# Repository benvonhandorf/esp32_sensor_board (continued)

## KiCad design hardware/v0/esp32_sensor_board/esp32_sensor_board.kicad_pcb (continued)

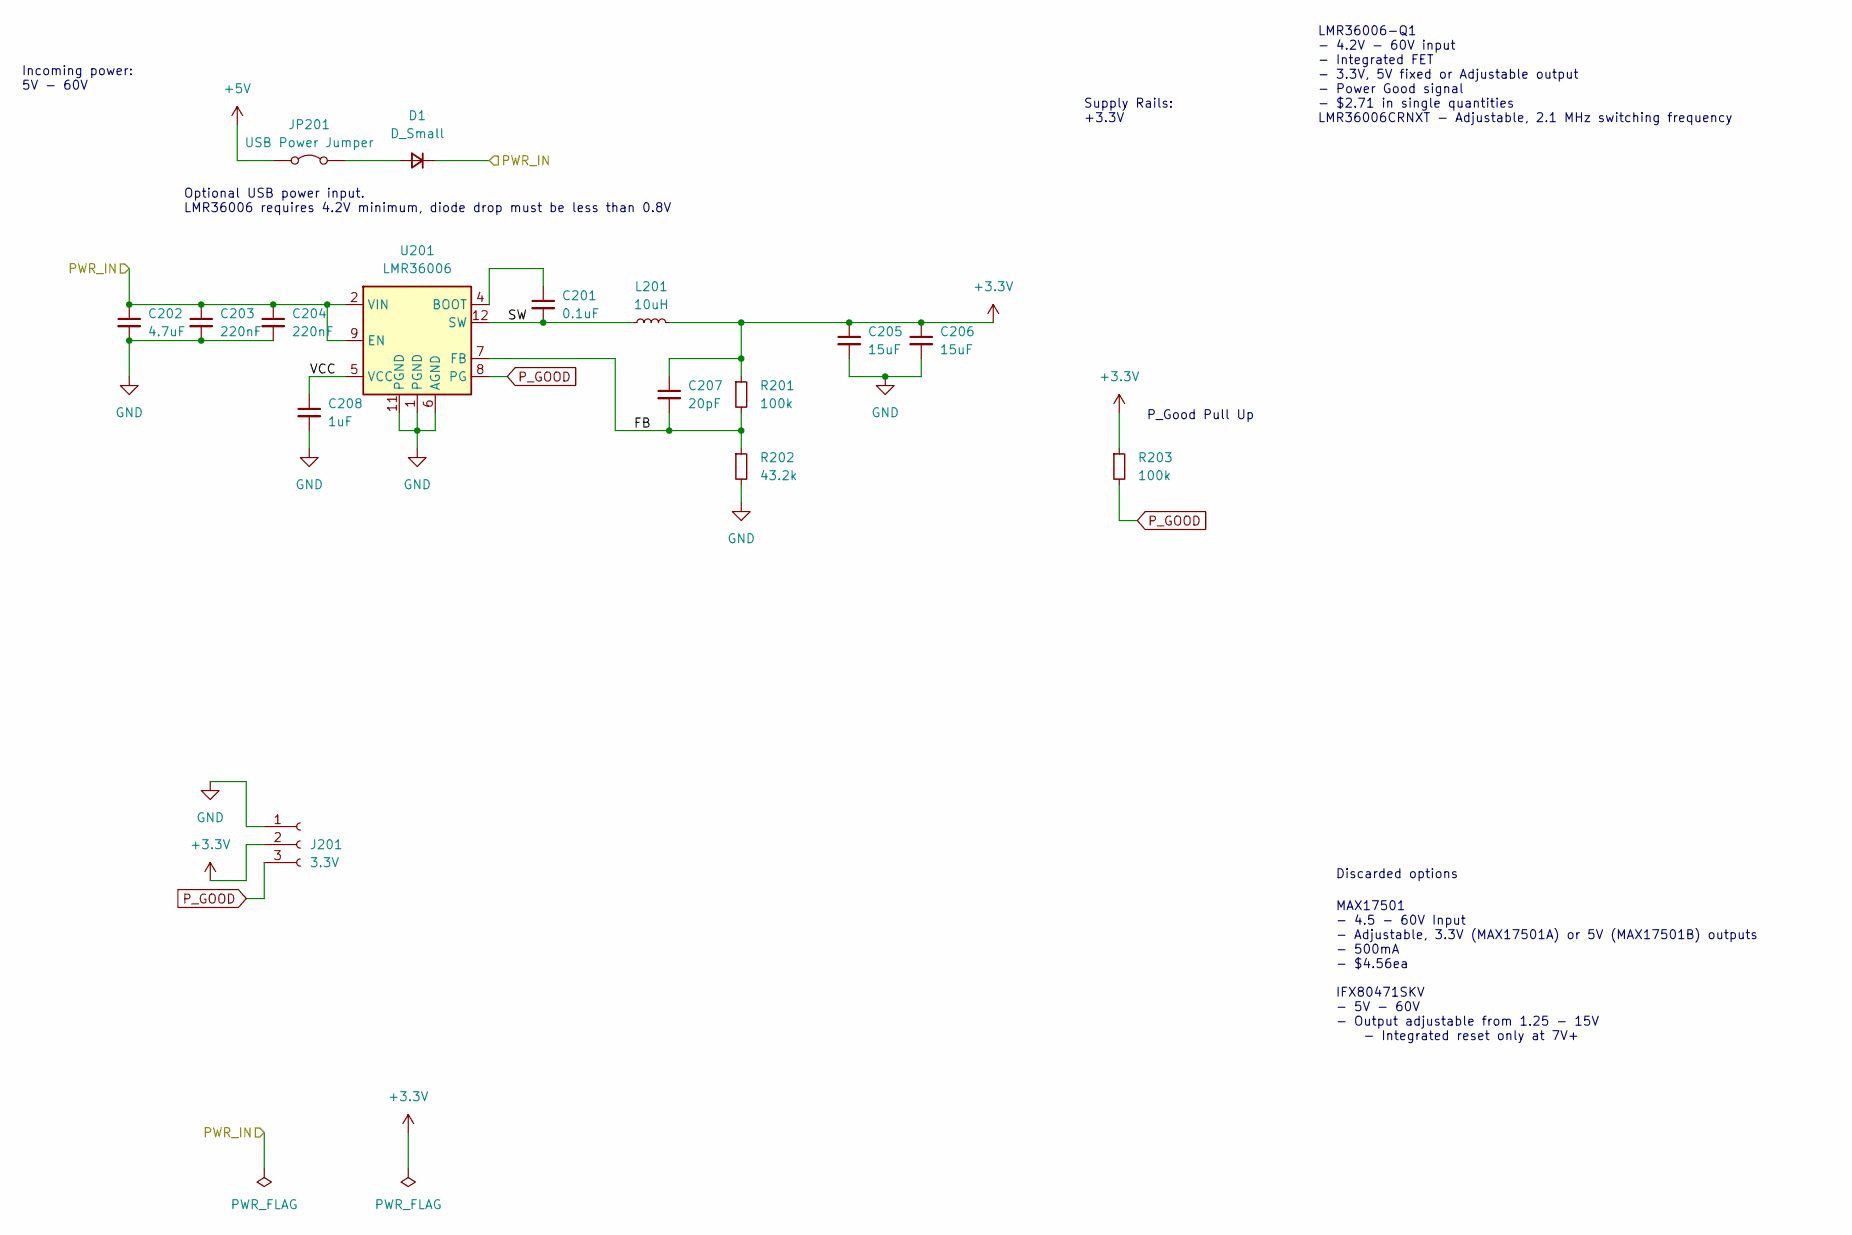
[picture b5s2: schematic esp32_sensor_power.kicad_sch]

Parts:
C201: 0.1uF; C_0603_1608Metric
C202: 4.7uF; C_1206_3216Metric
C203, C204: 220nF; C_1206_3216Metric
C205, C206: 15uF; C_1206_3216Metric
C207: 20pF; C_0805_2012Metric
C208: 1uF; C_0805_2012Metric
D1: D_Small; D_SOD-123
J201: 3.3V; PinHeader_1x03_P2.54mm_Vertical
JP201: USB Power Jumper; SolderJumper-2_P1.3mm_Bridged_RoundedPad1.0x1.5mm
L201: 10uH; L_Taiyo-Yuden_MD-4040
R201, R203: 100k; R_0603_1608Metric
R202: 43.2k; R_0603_1608Metric
U201: LMR36006; LMR36006-VQFN-HR

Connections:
+3.3V: C205.1, C206.1, C207.1, J201.2, L201.2, R201.1, R203.1; also elsewhere on the board
+5V: JP201.1 (A); also elsewhere on the board
/Power/FB: C207.2, R201.2, R202.1, U201.7 (FB)
/Power/SW: C201.2, L201.1, U201.3 (SW), U201.12 (SW)
/Power/VCC: C208.1, U201.5 (VCC)
GND: C202.2, C203.2, C204.2, C205.2, C206.2, C208.2, J201.1, R202.2, U201.1 (PGND), U201.6 (AGND), U201.11 (PGND); also elsewhere on the board
unnamed: D1.2 (A), JP201.2 (B)
unnamed: C201.1, U201.4 (BOOT)
P_GOOD: J201.3, R203.2, U201.8 (PG)
VIN: C202.1, C203.1, C204.1, D1.1 (K), U201.2 (VIN), U201.9 (EN), U201.10 (VIN); also elsewhere on the board

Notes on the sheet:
MAX17501 - 4.5 - 60V Input - Adjustable, 3.3V (MAX17501A) or 5V (MAX17501B) outputs - 500mA - $4.56ea
LMR36006-Q1 - 4.2V - 60V input - Integrated FET - 3.3V, 5V fixed or Adjustable output - Power Good signal - $2.71 in single quantities LMR36006CRNXT - Adjustable, 2.1 MHz switching frequency
IFX80471SKV - 5V - 60V - Output adjustable from 1.25 - 15V - Integrated reset only at 7V+
P_Good Pull Up
Discarded options
Optional USB power input. LMR36006 requires 4.2V minimum, diode drop must be less than 0.8V
Supply Rails: +3.3V
Incoming power: 5V - 60V

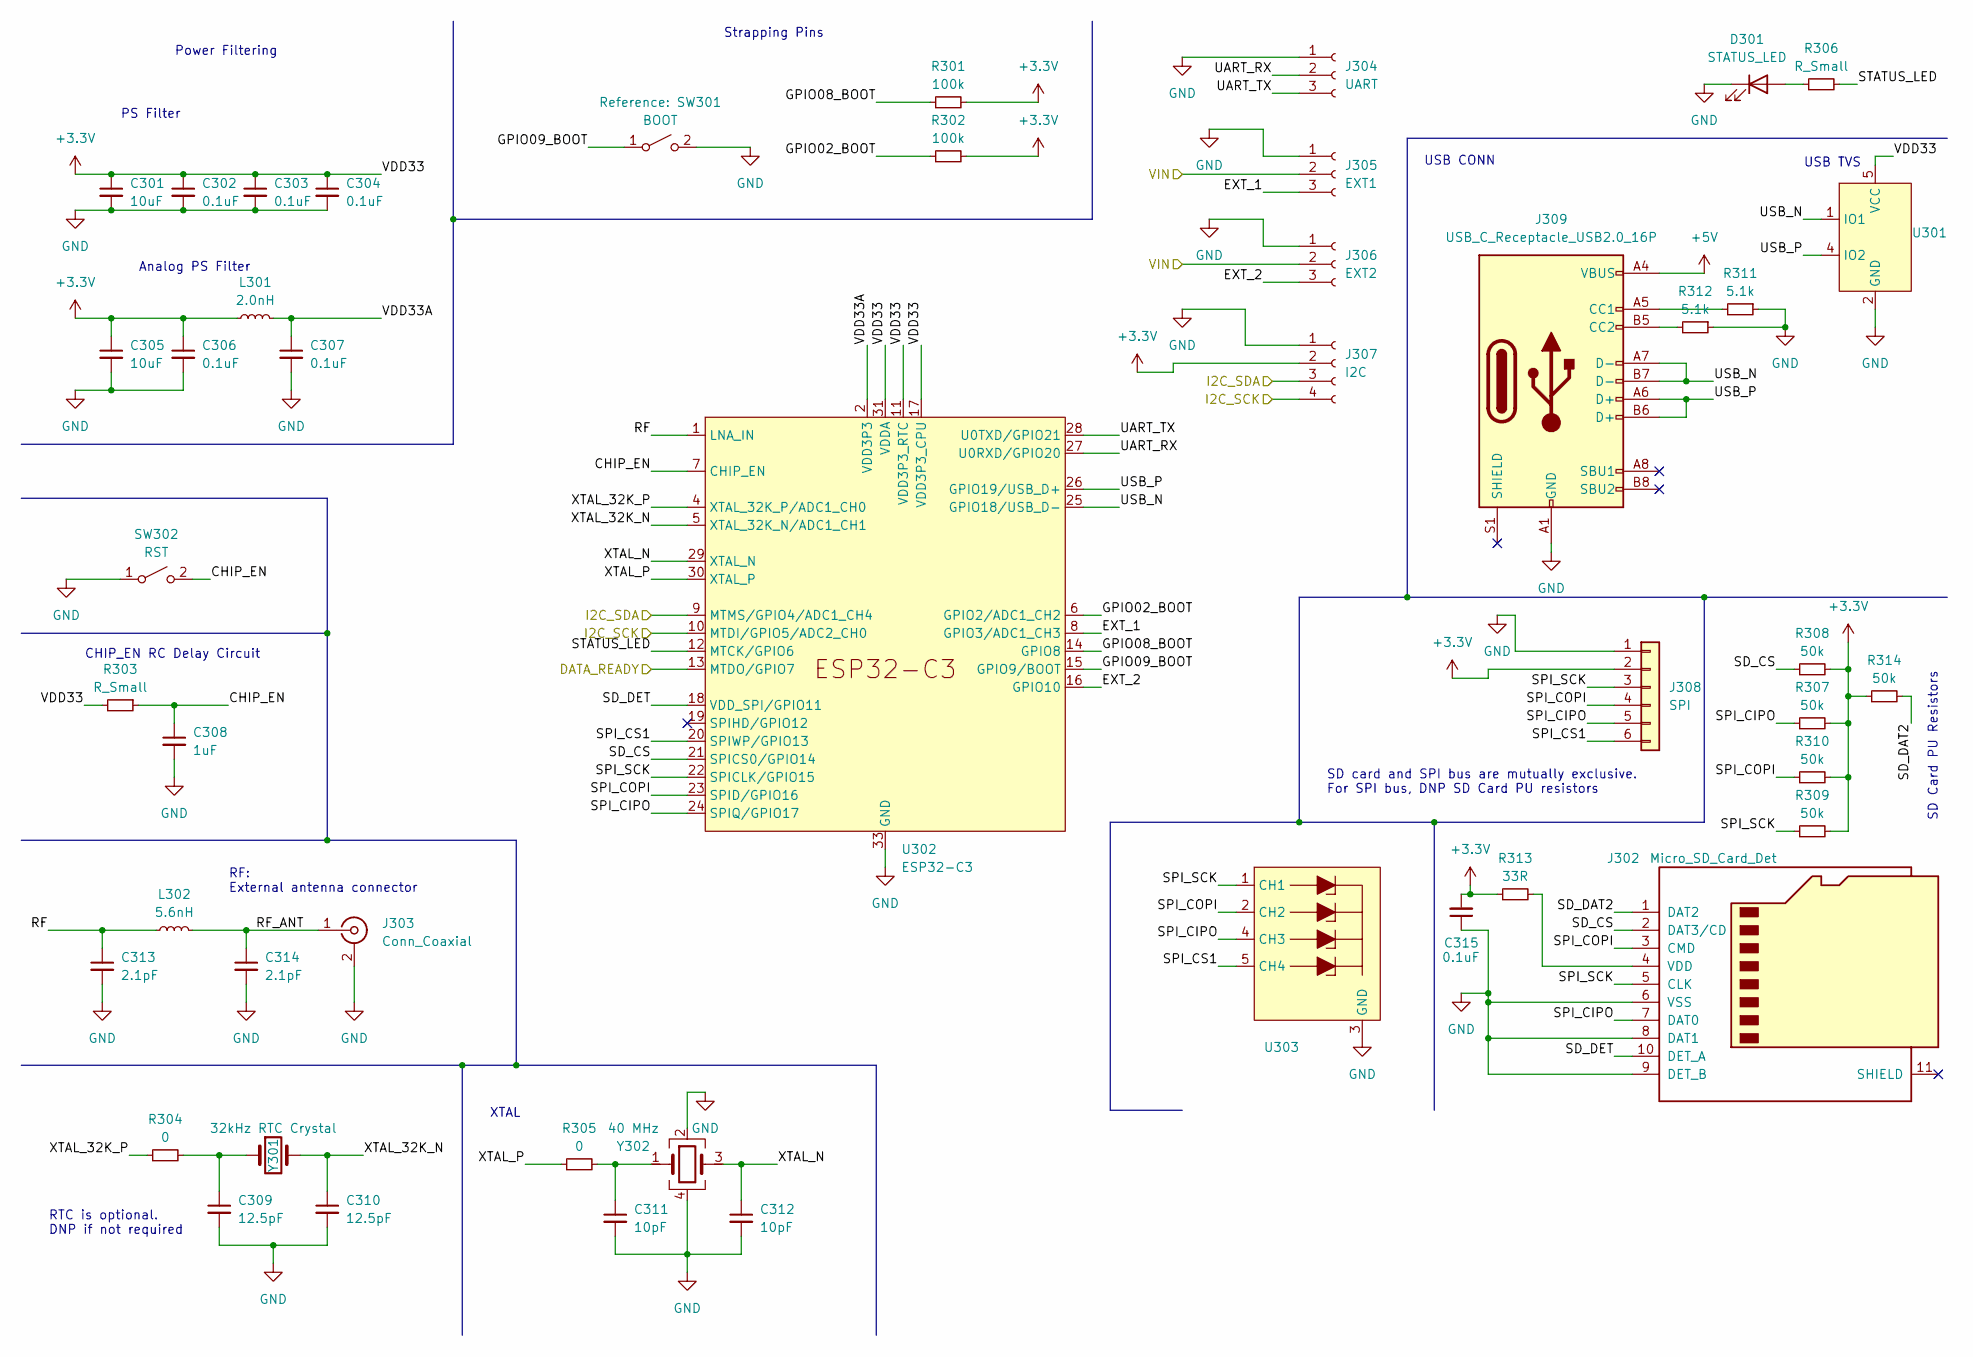
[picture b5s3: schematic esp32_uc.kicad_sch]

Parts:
C301, C305: 10uF; C_0805_2012Metric
C302, C303, C304, C306, C307, C315: 0.1uF; C_0603_1608Metric
C308: 1uF; C_0805_2012Metric
C309, C310: 12.5pF; C_0603_1608Metric
C311, C312: 10pF; C_0603_1608Metric
C313, C314: 2.1pF; C_0603_1608Metric
D301: STATUS_LED; LED_0805_2012Metric
J302: Micro_SD_Card_Det; MicroSD_Socket_Unbranded
J303: Conn_Coaxial; U.FL_Molex_MCRF_73412-0110_Vertical
J304: UART; PinHeader_1x03_P2.54mm_Vertical
J305: EXT1; PinHeader_1x03_P2.54mm_Vertical
J306: EXT2; PinHeader_1x03_P2.54mm_Vertical
J307: I2C; PinHeader_1x04_P2.54mm_Vertical
J308: SPI; PinHeader_1x06_P2.54mm_Vertical
J309: USB_C_Receptacle_USB2.0_16P; USB_C_Receptacle_GCT_USB4085
L301: 2.0nH; L_0402_1005Metric
L302: 5.6nH; L_0603_1608Metric
R301, R302: 100k; R_0603_1608Metric
R303, R306: R_Small; R_0603_1608Metric
R304, R305: 0; R_0603_1608Metric
R307, R308, R309, R310, R314: 50k; R_0603_1608Metric
R311, R312: 5.1k; R_0603_1608Metric
R313: 33R; R_0603_1608Metric
SW301: BOOT; TacButton_SMD_5mm_5mm
SW302: RST; Tac_SMD_6.4mm_Side_SPST_NO
U301: SOT-23-6
U302: ESP32-C3; QFN-32-1EP_5x5mm_P0.5mm_EP3.45x3.45mm
U303: Diode_10Pin_DFN2510A-10_10-XFDFN_SOT1176-1
Y301: 32kHz RTC Crystal; Crystal_SMD_3215-2Pin_3.2x1.5mm
Y302: 40 MHz; Crystal_SMD_2016-4Pin_2.0x1.6mm

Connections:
+3.3V: C301.1, C302.1, C303.1, C304.1, C305.1, C306.1, C315.2, J307.2, J308.2, L301.1, R301.2, R302.2, R303.2, R307.2, R308.2, R309.2, R310.2, R313.1, R314.1, U301.5 (VCC), U302.11 (VDD3P3_RTC), U302.17 (VDD3P3_CPU), U302.31 (VDDA), U302.32 (VDDA); also elsewhere on the board
+5V: J309.A4 (VBUS), J309.A9 (VBUS), J309.B4 (VBUS), J309.B9 (VBUS); also elsewhere on the board
/Load Cell Sensor/DRDY_NAU: U302.13 (MTDO/GPIO7); also elsewhere on the board
/Microprocessor/CHIP_EN: C308.1, R303.1, SW302.2 (B), U302.7 (CHIP_EN)
/Microprocessor/EXT_1: J305.3, U302.8 (GPIO3/ADC1_CH3)
/Microprocessor/EXT_2: J306.3, U302.16 (GPIO10)
/Microprocessor/GPIO02_BOOT: R302.1, U302.6 (GPIO2/ADC1_CH2)
/Microprocessor/GPIO08_BOOT: R301.1, U302.14 (GPIO8)
/Microprocessor/GPIO09_BOOT: SW301.1 (A), U302.15 (GPIO9/BOOT)
/Microprocessor/RF: C313.1, L302.1, U302.1 (LNA_IN)
/Microprocessor/RF_ANT: C314.1, J303.1 (In), L302.2
/Microprocessor/SD_CS: J302.2 (DAT3/CD), R308.1, U302.21 (SPICS0/GPIO14)
/Microprocessor/SD_DAT2: J302.1 (DAT2), R314.2
/Microprocessor/SD_DET: J302.10 (DET_A), U302.18 (VDD_SPI/GPIO11)
/Microprocessor/SPI_CIPO: J302.7 (DAT0), J308.5, R307.1, U302.24 (SPIQ/GPIO17), U303.4 (CH3)
/Microprocessor/SPI_COPI: J302.3 (CMD), J308.4, R310.1, U302.23 (SPID/GPIO16), U303.2 (CH2)
/Microprocessor/SPI_CS1: J308.6, U302.20 (SPIWP/GPIO13), U303.5 (CH4)
/Microprocessor/SPI_SCK: J302.5 (CLK), J308.3, R309.1, U302.22 (SPICLK/GPIO15), U303.1 (CH1)
/Microprocessor/STATUS_LED: R306.2, U302.12 (MTCK/GPIO6)
/Microprocessor/UART_RX: J304.2, U302.27 (U0RXD/GPIO20)
/Microprocessor/UART_TX: J304.3, U302.28 (U0TXD/GPIO21)
/Microprocessor/USB_N: J309.A7 (D-), J309.B7 (D-), U301.1 (IO1), U302.25 (GPIO18/USB_D-)
/Microprocessor/USB_P: J309.A6 (D+), J309.B6 (D+), U301.4 (IO2), U302.26 (GPIO19/USB_D+)
/Microprocessor/VDD33A: C307.1, L301.2, U302.2 (VDD3P3), U302.3 (VDD3P3)
/Microprocessor/XTAL_32K_N: C310.1, U302.5 (XTAL_32K_N/ADC1_CH1), Y301.2
/Microprocessor/XTAL_32K_P: R304.1, U302.4 (XTAL_32K_P/ADC1_CH0)
/Microprocessor/XTAL_N: C312.1, U302.29 (XTAL_N), Y302.3
/Microprocessor/XTAL_P: R305.1, U302.30 (XTAL_P)
/Power Measurement/I2C_SCL: J307.4, U302.10 (MTDI/GPIO5/ADC2_CH0); also elsewhere on the board
/Power Measurement/I2C_SDA: J307.3, U302.9 (MTMS/GPIO4/ADC1_CH4); also elsewhere on the board
GND: C301.2, C302.2, C303.2, C304.2, C305.2, C306.2, C307.2, C308.2, C309.2, C310.2, C311.2, C312.2, C313.2, C314.2, C315.1, D301.1 (K), J302.6 (VSS), J302.8 (DAT1), J302.9 (DET_B), J303.2 (Ext), J304.1, J305.1, J306.1, J307.1, J308.1, J309.A1 (GND), J309.A12 (GND), J309.B1 (GND), J309.B12 (GND), R311.1, R312.1, SW301.2 (B), SW302.1 (A), U301.2 (GND), U302.33 (GND), U303.3 (GND), U303.8 (GND), Y302.2, Y302.4; also elsewhere on the board
unnamed: C309.1, R304.2, Y301.1
unnamed: C311.1, R305.2, Y302.1
unnamed: D301.2 (A), R306.1
unnamed: J302.4 (VDD), R313.2
unnamed: J309.A5 (CC1), R311.2
unnamed: J309.B5 (CC2), R312.2
VIN: J305.2, J306.2; also elsewhere on the board

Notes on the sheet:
CHIP_EN RC Delay Circuit
Analog PS Filter
SD Card PU Resistors
XTAL
USB CONN
SD card and SPI bus are mutually exclusive. For SPI bus, DNP SD Card PU resistors
RTC is optional. DNP if not required
USB TVS
Strapping Pins
Power Filtering
PS Filter
RF: External antenna connector

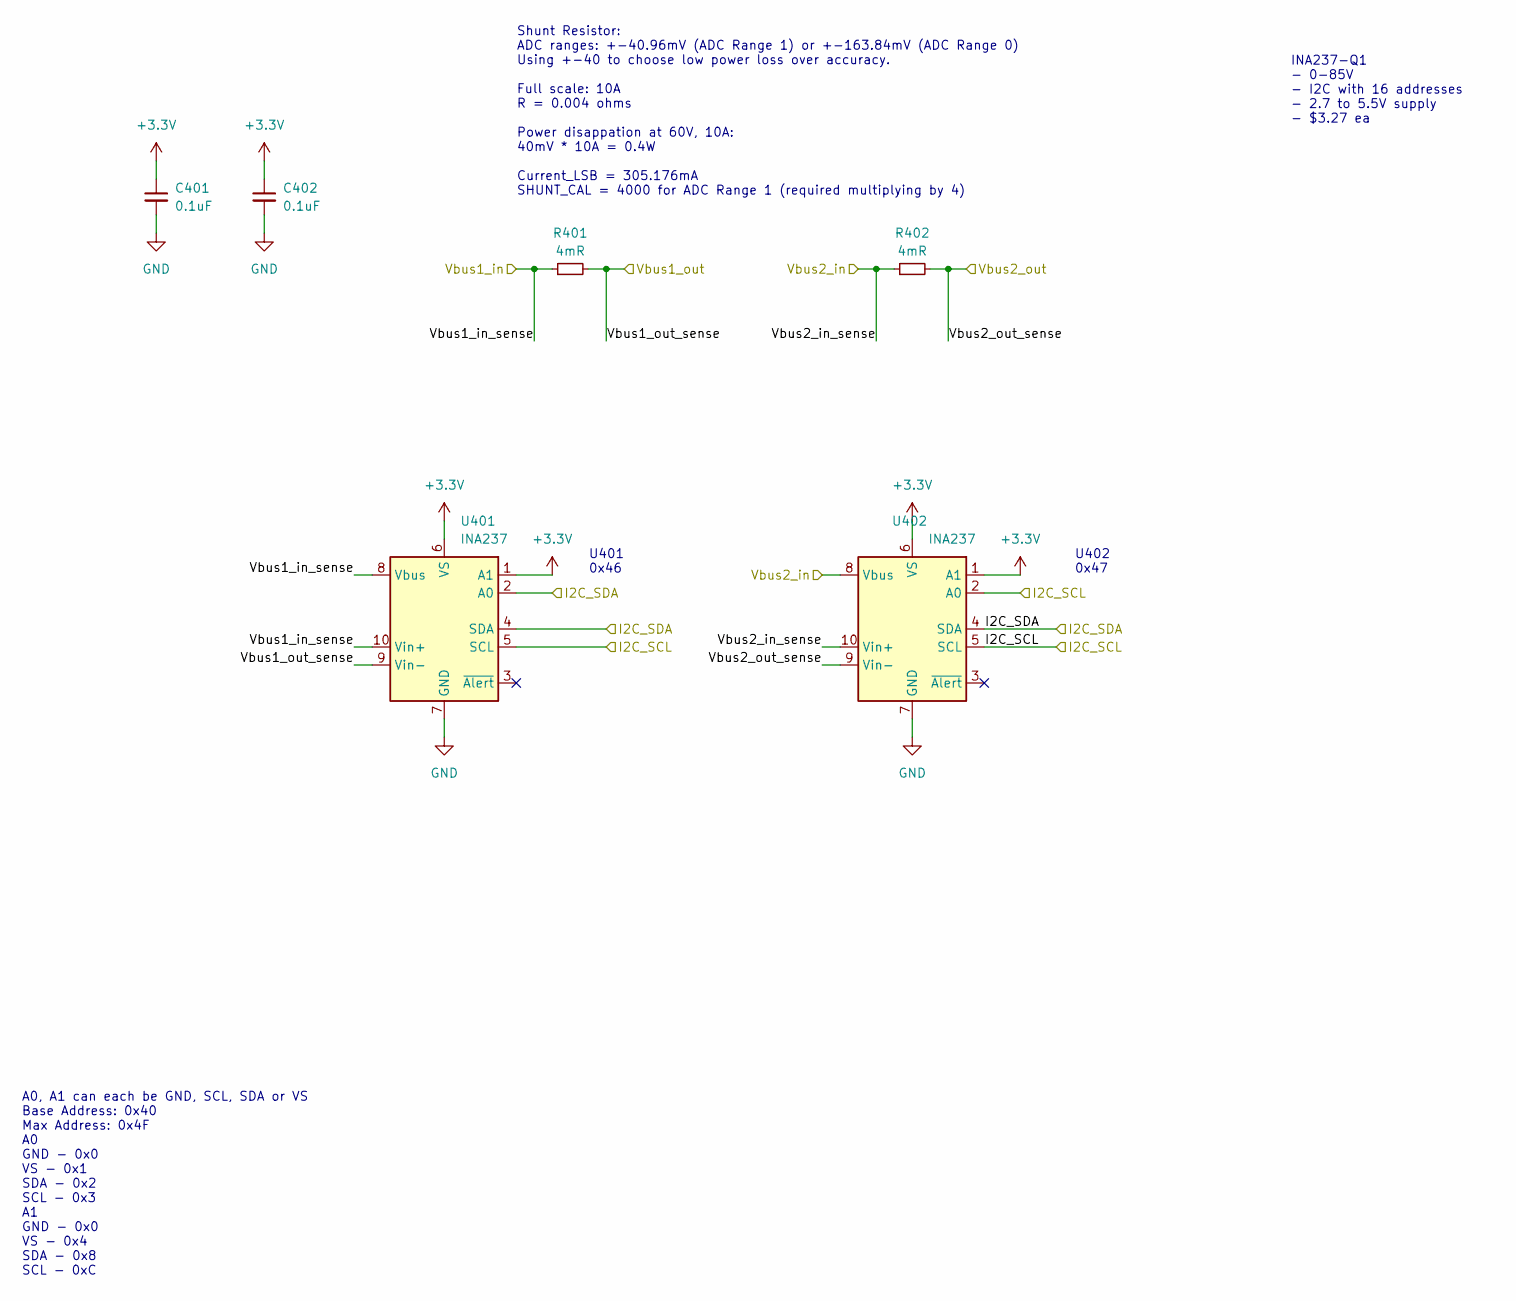
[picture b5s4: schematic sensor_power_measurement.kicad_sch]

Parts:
C401, C402: 0.1uF; C_0603_1608Metric
R401, R402: 4mR; R_2512_6332Metric
U401, U402: INA237; VSSOP-10_3x3mm_P0.5mm

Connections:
+3.3V: C401.1, C402.1, U401.1 (A1), U401.6 (VS), U402.1 (A1), U402.6 (VS); also elsewhere on the board
/Power Measurement/I2C_SCL: U401.5 (SCL), U402.2 (A0), U402.5 (SCL); also elsewhere on the board
/Power Measurement/I2C_SDA: U401.2 (A0), U401.4 (SDA), U402.4 (SDA); also elsewhere on the board
/Vbus1_in: R401.1, U401.8 (Vbus), U401.10 (Vin+); also elsewhere on the board
/Vbus2_in: R402.1, U402.8 (Vbus), U402.10 (Vin+); also elsewhere on the board
/Vbus2_out: R402.2, U402.9 (Vin-); also elsewhere on the board
GND: C401.2, C402.2, U401.7 (GND), U402.7 (GND); also elsewhere on the board
VIN: R401.2, U401.9 (Vin-); also elsewhere on the board

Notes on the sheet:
INA237-Q1 - 0-85V - I2C with 16 addresses - 2.7 to 5.5V supply - $3.27 ea
U402 0x47
Shunt Resistor: ADC ranges: +-40.96mV (ADC Range 1) or +-163.84mV (ADC Range 0) Using +-40 to choose low power loss over accuracy. Full scale: 10A R = 0.004 ohms Power disappation at 60V, 10A: 40mV * 10A = 0.4W Current_LSB = 305.176mA SHUNT_CAL = 4000 for ADC Range 1 (required multiplying by 4)
U401 0x46
A0, A1 can each be GND, SCL, SDA or VS Base Address: 0x40 Max Address: 0x4F A0 GND - 0x0 VS - 0x1 SDA - 0x2 SCL - 0x3 A1 GND - 0x0 VS - 0x4 SDA - 0x8 SCL - 0xC

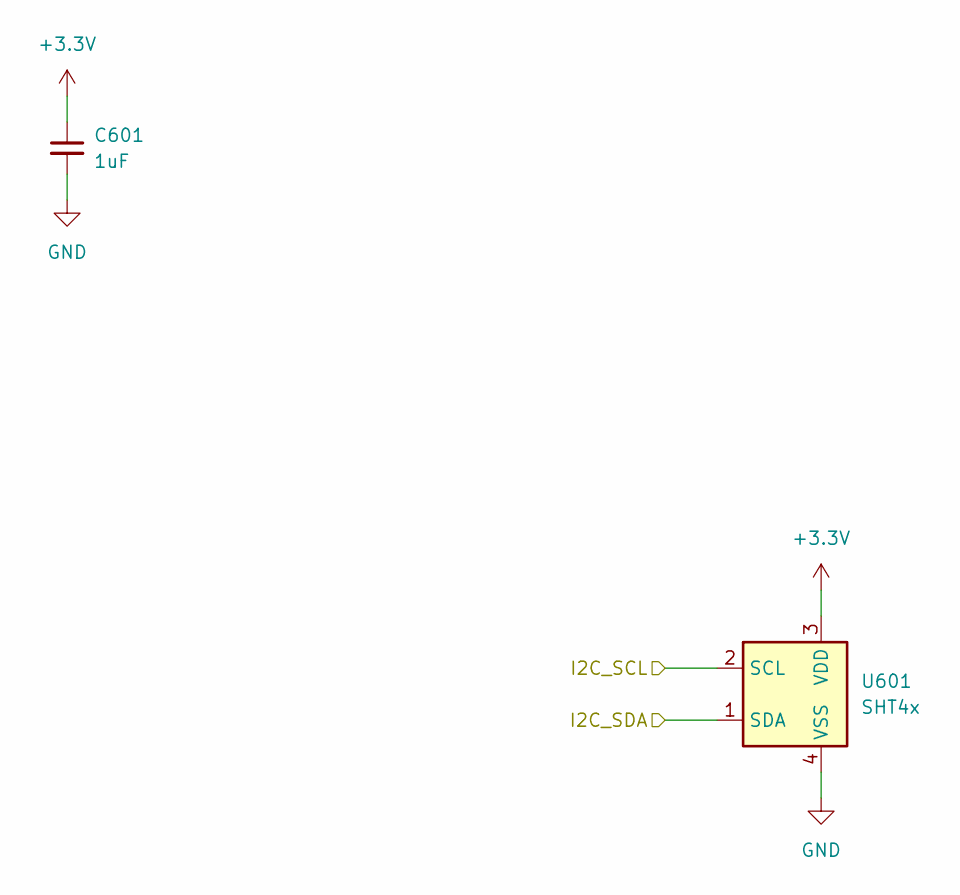
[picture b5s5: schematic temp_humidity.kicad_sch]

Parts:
C601: 1uF; C_0805_2012Metric
U601: SHT4x; Sensirion_DFN-4_1.5x1.5mm_P0.8mm_SHT4x_NoCentralPad

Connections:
+3.3V: C601.1, U601.3 (VDD); also elsewhere on the board
/Power Measurement/I2C_SCL: U601.2 (SCL); also elsewhere on the board
/Power Measurement/I2C_SDA: U601.1 (SDA); also elsewhere on the board
GND: C601.2, U601.4 (VSS); also elsewhere on the board

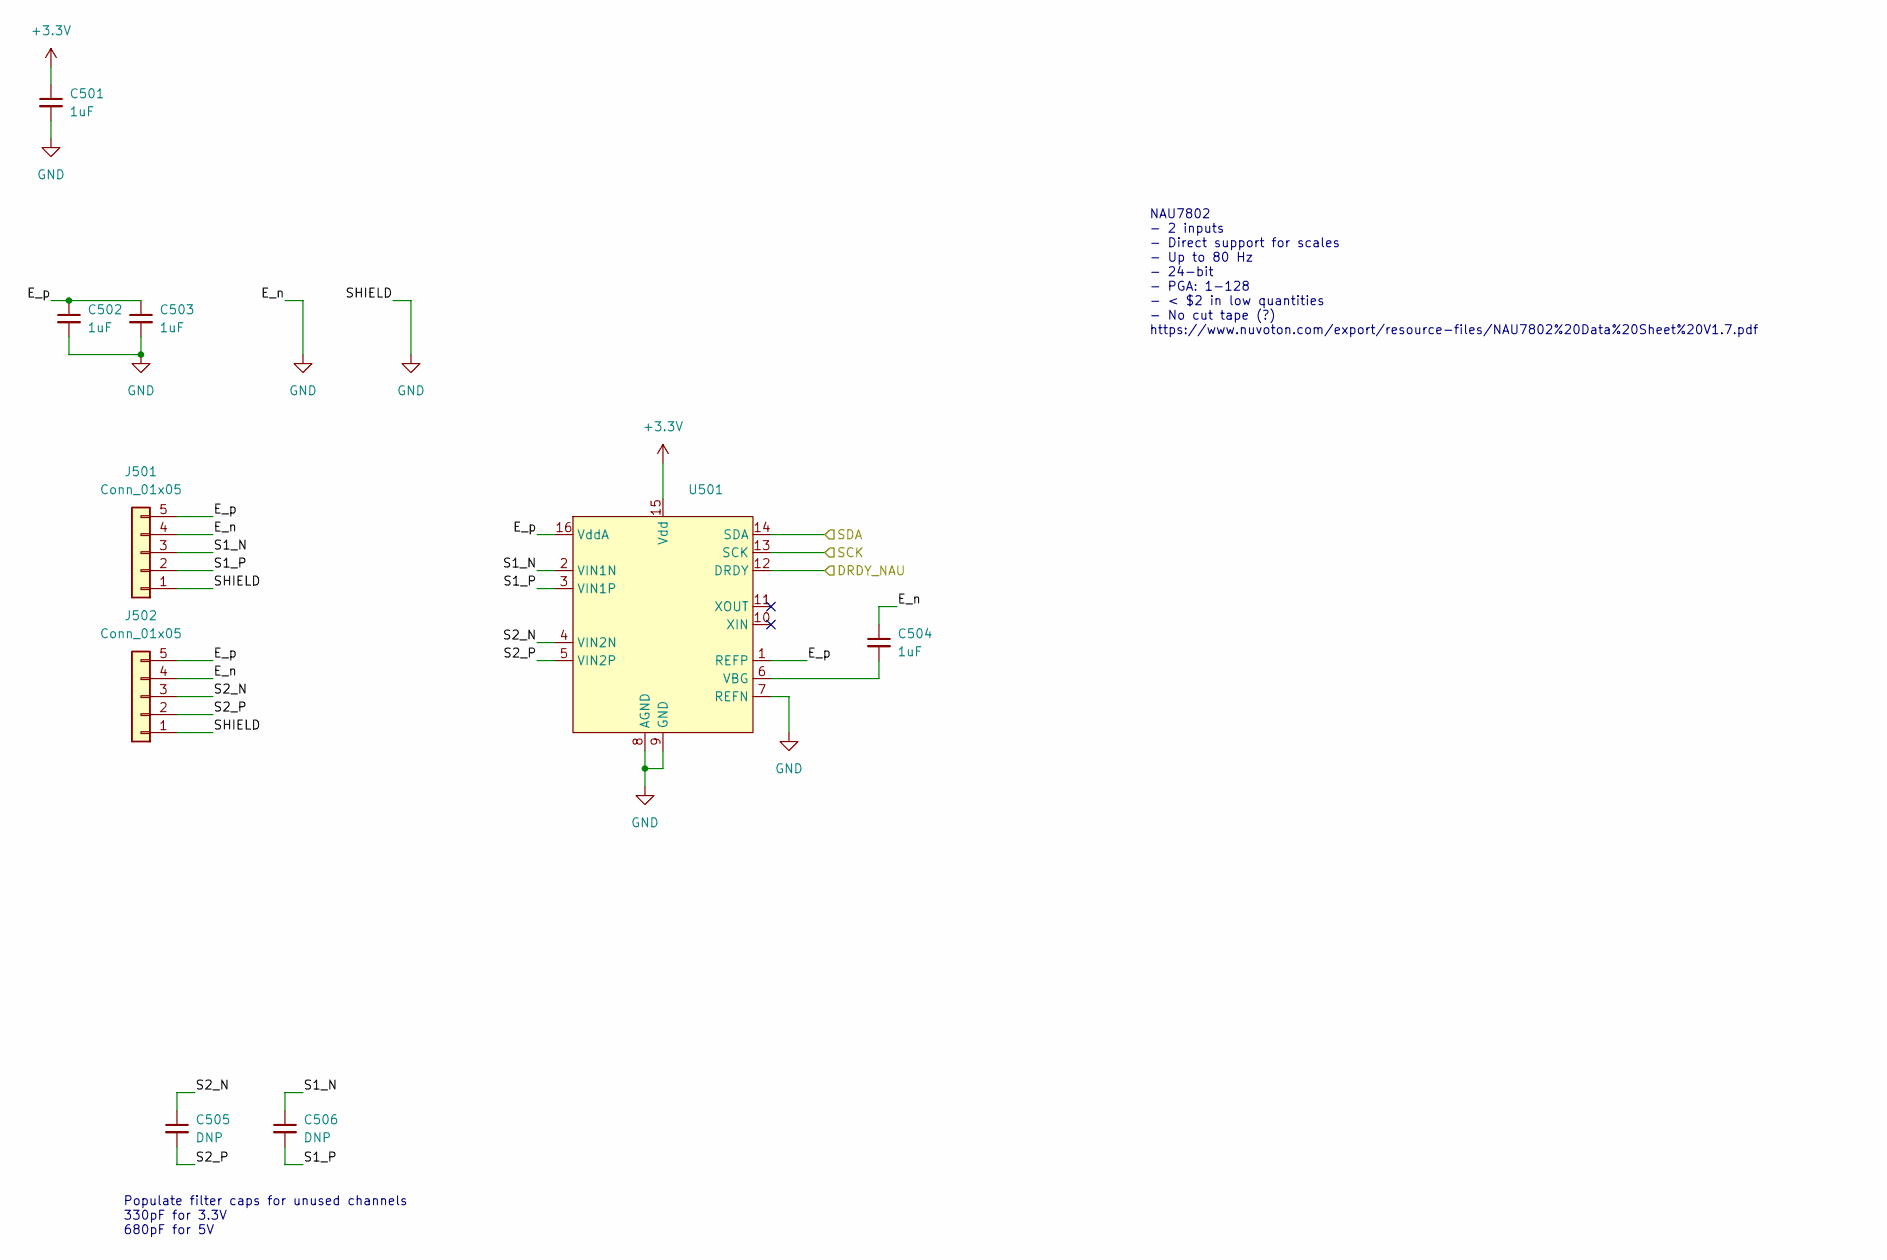
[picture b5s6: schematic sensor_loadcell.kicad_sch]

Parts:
C501, C502, C503, C504: 1uF; C_0805_2012Metric
C505, C506: DNP; C_0805_2012Metric
J501, J502: Conn_01x05; PinHeader_1x05_P2.54mm_Horizontal
U501: SOIC-16_3.9x9.9mm_P1.27mm

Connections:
+3.3V: C501.1, U501.15 (Vdd); also elsewhere on the board
/Load Cell Sensor/DRDY_NAU: U501.12 (DRDY); also elsewhere on the board
/Load Cell Sensor/E_p: C502.1, C503.1, J501.5, J502.5, U501.1 (REFP), U501.16 (VddA)
/Load Cell Sensor/S1_N: C506.1, J501.3, U501.2 (VIN1N)
/Load Cell Sensor/S1_P: C506.2, J501.2, U501.3 (VIN1P)
/Load Cell Sensor/S2_N: C505.1, J502.3, U501.4 (VIN2N)
/Load Cell Sensor/S2_P: C505.2, J502.2, U501.5 (VIN2P)
/Power Measurement/I2C_SCL: U501.13 (SCK); also elsewhere on the board
/Power Measurement/I2C_SDA: U501.14 (SDA); also elsewhere on the board
GND: C501.2, C502.2, C503.2, C504.1, J501.1, J501.4, J502.1, J502.4, U501.7 (REFN), U501.8 (AGND), U501.9 (GND); also elsewhere on the board
unnamed: C504.2, U501.6 (VBG)

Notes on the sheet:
NAU7802 - 2 inputs - Direct support for scales - Up to 80 Hz - 24-bit - PGA: 1-128 - < $2 in low quantities - No cut tape (?) https://www.nuvoton.com/export/resource-files/NAU7802%20Data%20Sheet%20V1.7.pdf
Populate filter caps for unused channels 330pF for 3.3V 680pF for 5V

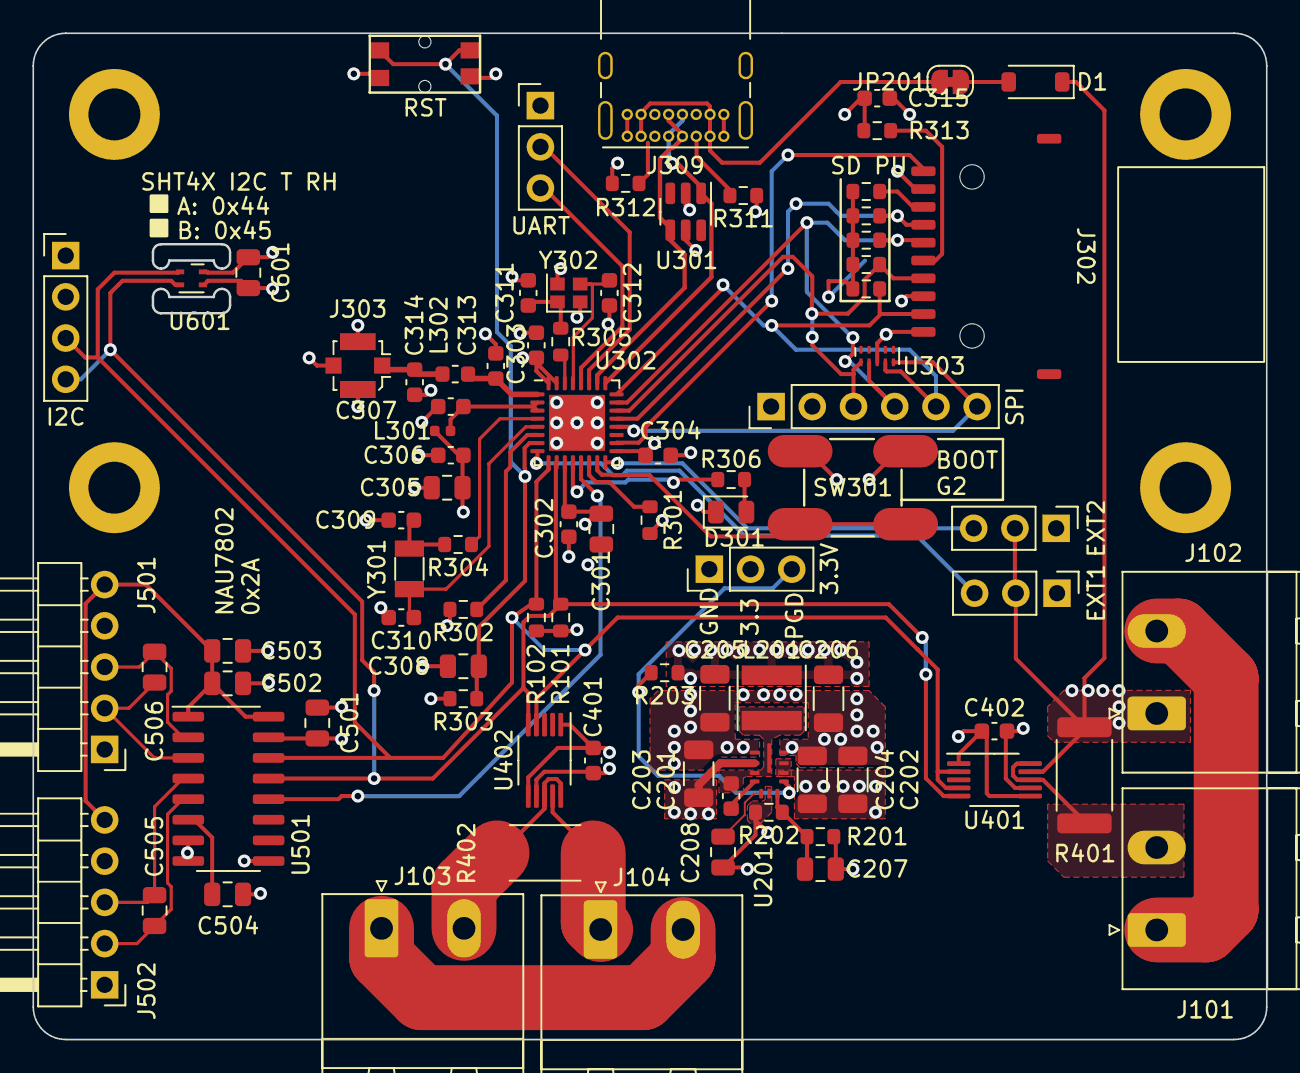
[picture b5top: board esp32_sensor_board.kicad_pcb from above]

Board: 4 copper layers, 76.0 x 62.0 mm, 90 parts (0 on the bottom side), 53 nets.

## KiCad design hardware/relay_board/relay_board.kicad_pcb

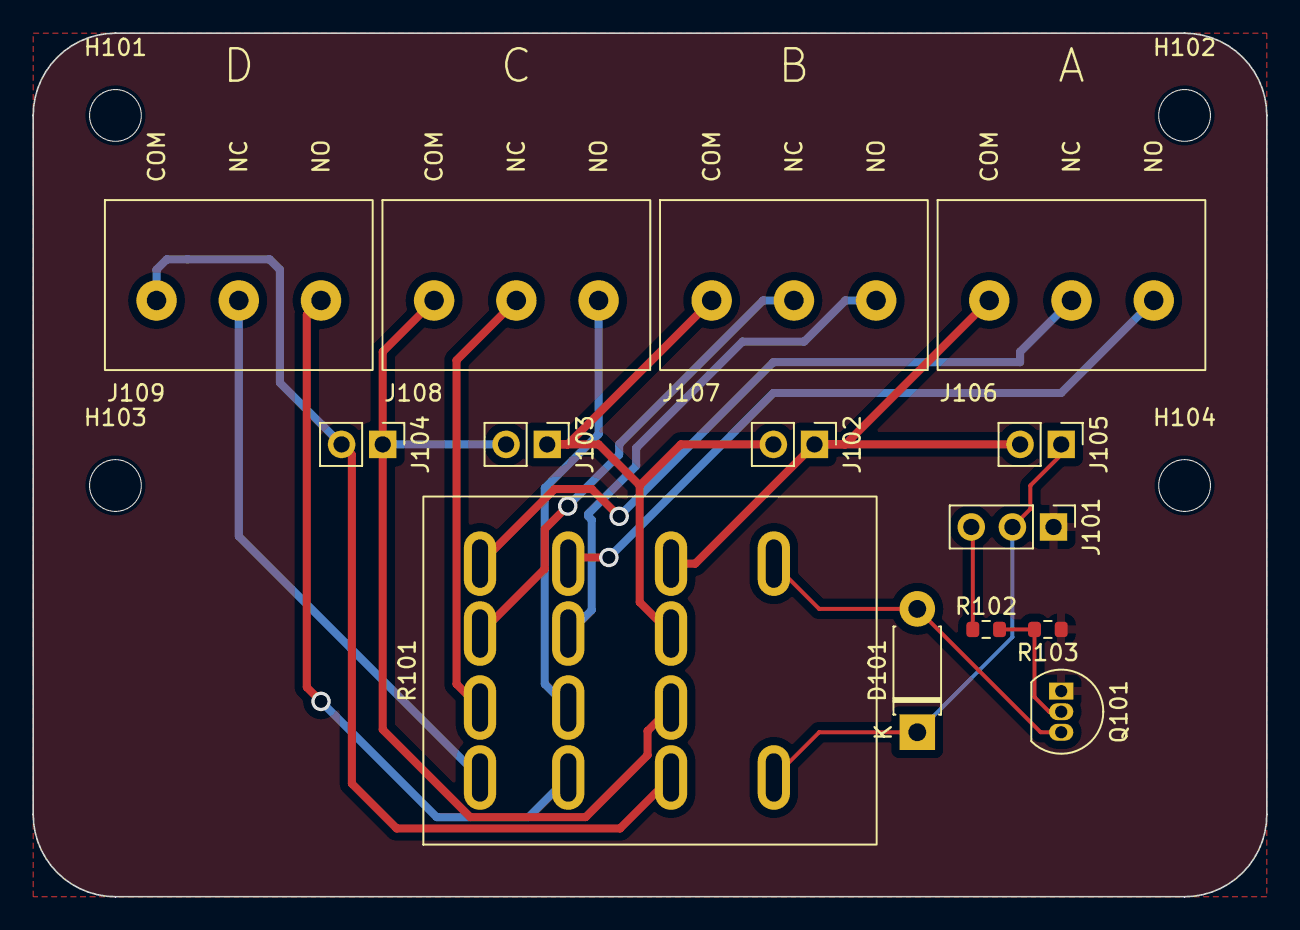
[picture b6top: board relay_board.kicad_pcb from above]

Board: 2 copper layers, 76.2 x 53.3 mm, 18 parts (0 on the bottom side), 17 nets.

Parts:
D101: D; D_DO-41_SOD81_P7.62mm_Horizontal
H101, H102, H103, H104: MountingHole; MountingHole_3.2mm_M3
J101: Conn_01x03_Pin; PinHeader_1x03_P2.54mm_Vertical
J102: A - B; PinHeader_1x02_P2.54mm_Vertical
J103: B - C; PinHeader_1x02_P2.54mm_Vertical
J104: C - D; PinHeader_1x02_P2.54mm_Vertical
J105: VIN - A; PinHeader_1x02_P2.54mm_Vertical
J106: A; 5.08mm_THT_PinHeader_01x03
J107: B; 5.08mm_THT_PinHeader_01x03
J108: C; 5.08mm_THT_PinHeader_01x03
J109: D; 5.08mm_THT_PinHeader_01x03
Q101: 2N7000; TO-92_Inline
R101: OMRON_MY4
R102: 1k; R_0603_1608Metric
R103: 100k; R_0603_1608Metric

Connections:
/COM_A: J102.1, J105.2, J106.1, R101.9 (COM)
/COM_B: J102.2, J103.1, J107.1, R101.10 (COM)
/COM_C: J103.2, J104.1, J108.1, R101.11 (COM)
/COM_D: J104.2, J109.1, R101.12 (COM)
/NC_A: J106.2, R101.1 (NC)
/NC_B: J107.2, R101.2 (NC)
/NC_C: J108.2, R101.3 (NC)
/NC_D: J109.2, R101.4 (NC)
/NO_A: J106.3, R101.5 (NO)
/NO_B: J107.3, R101.6 (NO)
/NO_C: J108.3, R101.7 (NO)
/NO_D: J109.3, R101.8 (NO)
/SIG: J101.3, R102.1
GND: J101.1, Q101.1 (S), R103.1
unnamed: D101.2 (A), Q101.3 (D), R101.13 (-)
unnamed: Q101.2 (G), R102.2, R103.2
VSS: D101.1 (K), J101.2, J105.1, R101.14 (+)

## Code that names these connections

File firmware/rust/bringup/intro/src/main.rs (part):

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    let mut wifi = wifi_init(peripherals.modem, sys_loop);
    wifi_scan(&mut wifi);

    let scl = peripherals.pins.gpio5;
    let sda = peripherals.pins.gpio4;

    let i2c_config = I2cConfig::new().baudrate(100.kHz().into());
    let i2c_bus_raw = I2cDriver::new(peripherals.i2c0, sda, scl, &i2c_config).unwrap();
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
    let spi = peripherals.spi2;

    let sck = peripherals.pins.gpio15;
    let cipo = peripherals.pins.gpio17;
    let copi = peripherals.pins.gpio16;
    let sd_cs = peripherals.pins.gpio14;
    let mut sd_det = PinDriver::input(peripherals.pins.gpio11).unwrap();

    sd_det.set_pull(Pull::Up).unwrap();

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    //     &sdcard_config
    // ).unwrap();

    // let sdcard = embedded_sdmmc::SdCard::new(sd_device, PinDriver::output(sd_cs).unwrap(), FreeRtos);

    // info!("SD Card Type: {}", sdcard.get_card_type().unwrap() as u8);

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
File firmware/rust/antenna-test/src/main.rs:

use log::*;
use embedded_svc:: {
    wifi::Configuration,
    wifi::ClientConfiguration,
};
use esp_idf_hal::{
    delay::{FreeRtos, Delay},
    i2c::{I2cConfig, I2cDriver},
    peripherals::Peripherals,
    prelude::*,
    spi::*,
    gpio::{
        AnyOutputPin,
        PinDriver,
    },
};
use esp_idf_svc::{
    eventloop::EspSystemEventLoop, 
    nvs::EspDefaultNvsPartition, 
    wifi::BlockingWifi, 
    wifi::EspWifi,
};
use esp_idf_sys as _; // If using the `binstart` feature of `esp-idf-sys`, always keep this module imported

use embedded_sdmmc::*;

fn main() {
    // It is necessary to call this function once. Otherwise some patches to the runtime
    // implemented by esp-idf-sys might not link properly. See https://github.com/esp-rs/esp-idf-template/issues/71
    esp_idf_sys::link_patches();
    // Bind the log crate to the ESP Logging facilities
    esp_idf_svc::log::EspLogger::initialize_default();

    let peripherals = Peripherals::take().unwrap();

    let sys_loop = EspSystemEventLoop::take().unwrap();
    let nvs = EspDefaultNvsPartition::take().unwrap();

    let spi = peripherals.spi2;

    /*
    #define CONFIG_EXAMPLE_PIN_MOSI 9
#define CONFIG_EXAMPLE_PIN_MISO 8
#define CONFIG_EXAMPLE_PIN_CLK 7
#define CONFIG_EXAMPLE_PIN_CS 21
 */

    let sck = peripherals.pins.gpio7; //D8
    let cipo = peripherals.pins.gpio8; //D9
    let copi = peripherals.pins.gpio9; //D10
    let sd_cs = peripherals.pins.gpio21; //D2
    // let mut sd_det = PinDriver::input(peripherals.pins.gpio11).unwrap();

    // sd_det.set_pull(Pull::Up).unwrap();

    // let has_sd = sd_det.get_level();

    // if has_sd == esp_idf_hal::gpio::Level::Low {
    //     info!("SD Card Detected");
    // } else {
    //     info!("No SD Card Detected");
    // }

    //cargo build --bin launch --features launch --target .vscode --profile debug-no-opt

    let driver_config = SpiDriverConfig::new();

        info!("Initializing SD Card");

        let spi_driver = SpiDriver::new(spi,
        sck,
        copi,
        Some(cipo),
        &driver_config
        ).unwrap();

        info!("Preparing SD Card");

        let sdcard_config = config::Config::new().baudrate(26.MHz().into());

        let sd_device = SpiDeviceDriver::new(
            &spi_driver,
            None::<AnyOutputPin>,
            &sdcard_config
        ).unwrap();

        let sdcard = embedded_sdmmc::SdCard::new(sd_device, PinDriver::output(sd_cs).unwrap(), FreeRtos);

        let card_type = sdcard.get_card_type();

        if card_type.is_some() {
            info!("SD Card Type: {}", card_type.unwrap() as u8);
        }

        let num_bytes = sdcard.num_bytes();

        if num_bytes.is_ok() {
            info!("SD Card Size: {}", num_bytes.unwrap());
        }

    let mut wifi = BlockingWifi::wrap(
        EspWifi::new(peripherals.modem, sys_loop.clone(), None).unwrap(),
        sys_loop,
    ).unwrap();

    let _ = wifi.set_configuration(&Configuration::Client(ClientConfiguration::default()));

    wifi.start().unwrap();

    let scan_result = wifi.scan();

    if scan_result.is_err() {
        error!("Scan Failed: {:x?}", scan_result);
    }

    info!("Scan Result: {:?}", scan_result.unwrap());
}

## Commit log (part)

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2023-07-20 Schematic WIP
2023-07-20 Remove lock file
2023-07-20 Clean up errors
2023-08-14 PCB ordered, a few initial mistakes fixed
2023-08-14 Rust board bringup WIP
2023-08-27 WIP INA237
2023-09-26 Gitignore
2023-10-16 Board refactor WIP. Still needs PU resistors
2023-10-16 Remove lockfiles
2023-10-24 TVS and PU work
2023-10-31 Relay board, firmware tests
2024-05-27 Update project, build working
2024-06-02 INA237 progress, SHT4X comms working
2024-06-04 INA237 A communication working
2024-06-20 Current unit fix
2024-06-21 NAU7802 initial work
2024-07-05 NAU7802 ADC working
2024-07-06 Before Embassy Integration
2024-07-06 Clean up driver crate warnings
2024-07-11 WIP v3 hardware
2024-10-20 Output files
2024-11-28 Layout WIP
2025-01-12 Revisions for recordering
